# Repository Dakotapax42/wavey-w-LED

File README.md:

# wavey-w-LED

temporary repository until I finalize things :)

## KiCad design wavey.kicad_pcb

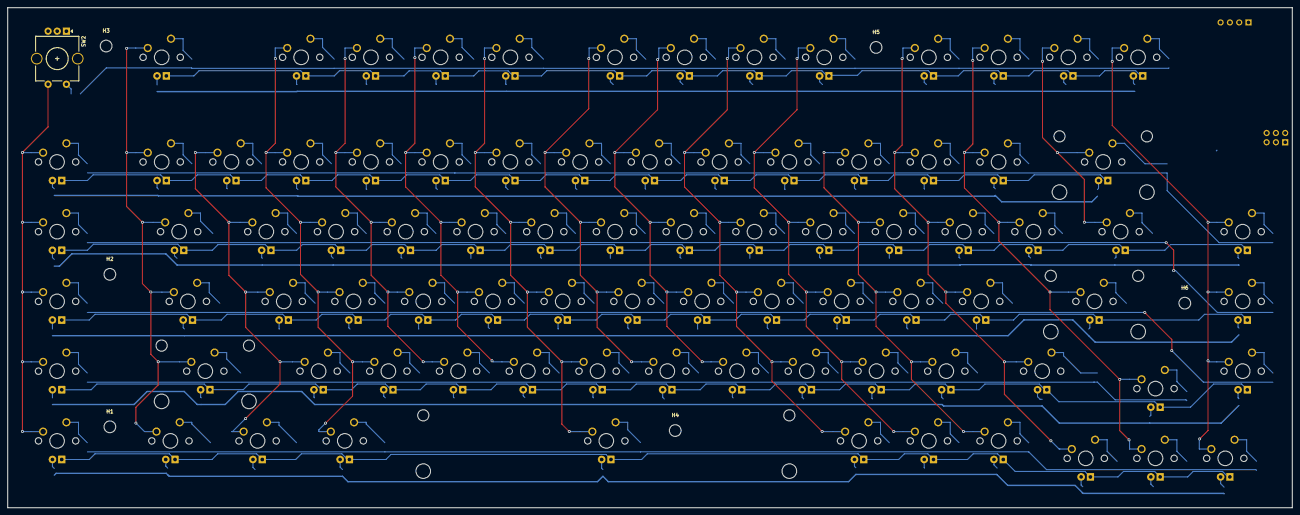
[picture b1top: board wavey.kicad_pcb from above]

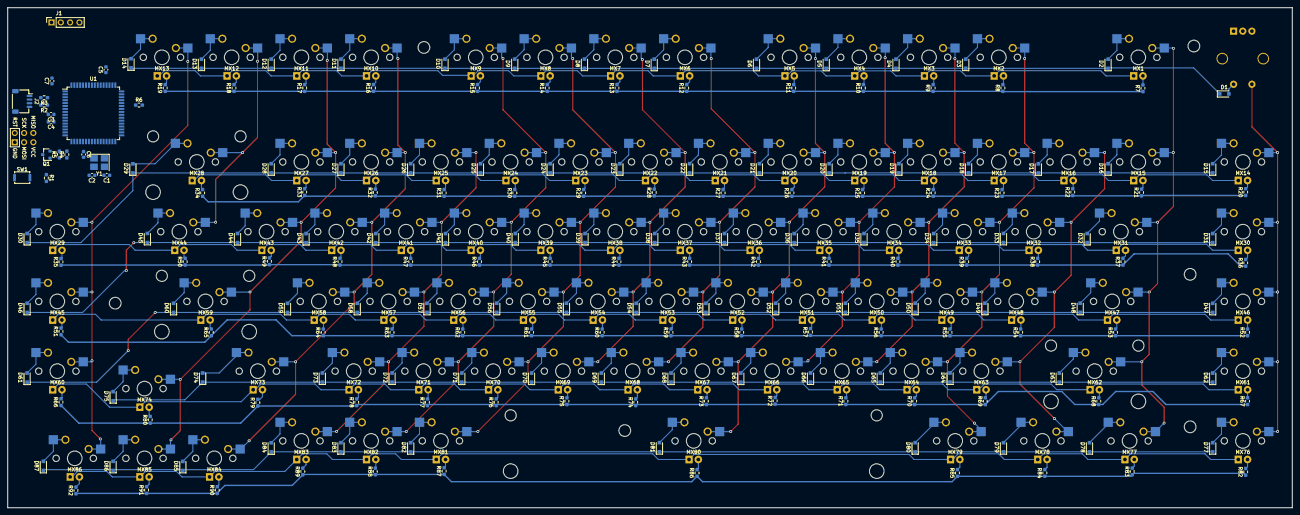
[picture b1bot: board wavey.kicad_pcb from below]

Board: 2 copper layers, 350.9 x 136.6 mm, 283 parts (191 on the bottom side), 214 nets.

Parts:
C1, C2: 22pF; C_0603_1608Metric
C3: 1uF; C_0603_1608Metric
C4, C5, C6: 0.1uF; C_0603_1608Metric
C7: 10uF; C_0603_1608Metric
D1, D2, D3, D4, D5, D6, D7, D8, D9, D10, D11, D12, D13, D14, D15, D16, D17, D18, D19, D20, D21, D22, D23, D24, D25, D26, D27, D28, D29, D30, D31, D32, D33, D34, D35, D36, D37, D38, D39, D40, D41, D42, D43, D44, D45, D46, D47, D48, D49, D50, D51, D52, D53, D54, D55, D56, D57, D58, D59, D60, D61, D62, D63, D64, D65, D66, D67, D68, D69, D70, D71, D72, D73, D74, D75, D77, D78, D79, D80, D81, D82, D83, D84, D85, D86, D87: D_Small; D_SOD-323_HandSoldering
H1, H2, H3, H4, H5, H6: MountingHole; MountingHole_3.2mm_M3
J1: Conn_01x04; PinSocket_1x04_P2.54mm_Vertical
J2: Conn_01x04; JST_SH_SM04B-SRSS-TB_1x04-1MP_P1.00mm_Horizontal
J3: AVR-ISP-6; Reset_Pretty-Mask
MX1, MX2, MX3, MX4, MX5, MX6, MX7, MX8, MX9, MX10, MX11, MX12, MX13, MX14, MX15, MX16, MX17, MX18, MX19, MX20, MX21, MX22, MX23, MX24, MX25, MX26, MX27, MX29, MX30, MX32, MX33, MX34, MX35, MX36, MX37, MX38, MX39, MX40, MX41, MX42, MX43, MX45, MX46, MX48, MX49, MX50, MX51, MX52, MX53, MX54, MX55, MX56, MX57, MX58, MX60, MX61, MX63, MX64, MX65, MX66, MX67, MX68, MX69, MX70, MX71, MX72, MX74, MX76, MX81, MX82, MX83, MX84, MX85, MX86: MX-LED; MXOnly-1U-Hotswap
MX28: MX-LED; MXOnly-2U-Hotswap
MX31, MX44: MX-LED; MXOnly-1.5U-Hotswap
MX47, MX73: MX-LED; MXOnly-1.75U-Hotswap
MX59, MX62: MX-LED; MXOnly-2.25U-Hotswap
MX77, MX78, MX79: MX-LED; MXOnly-1.25U-Hotswap
MX80: MX-LED; MXOnly-6.25U-Hotswap
Q1: AO3400A; SOT-23
R1, R5: 10k; R_0603_1608Metric_Pad0.98x0.95mm_HandSolder
R2, R3: 22; R_0603_1608Metric_Pad0.98x0.95mm_HandSolder
R4, R7, R8, R9, R10, R11, R12, R13, R14, R15, R16, R17, R18, R19, R20, R21, R22, R23, R24, R25, R26, R27, R28, R29, R30, R31, R32, R33, R34, R35, R36, R37, R38, R39, R40, R41, R42, R43, R44, R45, R46, R47, R48, R49, R50, R51, R52, R53, R54, R55, R56, R57, R58, R59, R60, R61, R62, R63, R64, R65, R66, R67, R68, R69, R70, R71, R72, R73, R74, R75, R76, R77, R78, R79, R80, R82, R83, R84, R85, R86, R87, R88, R89, R90, R91, R92: 470; R_0603_1608Metric_Pad0.98x0.95mm_HandSolder
R6: 1k; R_0603_1608Metric_Pad0.98x0.95mm_HandSolder
SW1: SW_Push; SW_Push_SPST_NO_Alps_SKRK
SW2: Rotary_Encoder_Switch; RotaryEncoder_Alps_EC11E-Switch_Vertical_H20mm_CircularMoun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
U1: AT90USB1286-AU; TQFP-64_14x14mm_P0.8mm
Y1: 16Mhz; Crystal_SMD_3225-4Pin_3.2x2.5mm_HandSoldering

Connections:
+5V: C4.1, C5.1, C6.1, C7.1, J1.3, J2.1, J3.2, R1.1, R7.1, R8.1, R9.1, R10.1, R11.1, R12.1, R13.1, R14.1, R15.1, R16.1, R17.1, R18.1, R19.1, R20.1, R21.1, R22.1, R23.1, R24.1, R25.1, R26.1, R27.1, R28.1, R29.1, R30.1, R31.1, R32.1, R33.1, R34.1, R35.1, R36.1, R37.1, R38.1, R39.1, R40.1, R41.1, R42.1, R43.1, R44.1, R45.1, R46.1, R47.1, R48.1, R49.1, R50.1, R51.1, R52.1, R53.1, R54.1, R55.1, R56.1, R57.1, R58.1, R59.1, R60.1, R61.1, R62.1, R63.1, R64.1, R65.1, R66.1, R67.1, R68.1, R69.1, R70.1, R71.1, R72.1, R73.1, R74.1, R75.1, R76.1, R77.1, R78.1, R79.1, R80.1, R82.1, R83.1, R84.1, R85.1, R86.1, R87.1, R88.1, R89.1, R90.1, R91.1, R92.1, U1.3, U1.8, U1.21, U1.52, U1.64
/MCU_D+: R2.1, U1.5
/MCU_D-: R3.1, U1.4
A1: SW2.A, U1.14
B1: SW2.B, U1.15
D+: J2.3, R2.2
D-: J2.2, R3.2
GND: C1.2, C2.1, C3.2, C4.2, C5.2, C6.2, C7.2, J1.4, J2.4, J3.6, Q1.2, R5.2, R6.2, SW1.1, SW2.C, U1.6, U1.22, U1.53, U1.63, Y1.2, Y1.4
LEGEND: MX1.4, MX2.4, MX3.4, MX4.4, MX5.4, MX6.4, MX7.4, MX8.4, MX9.4, MX10.4, MX11.4, MX12.4, MX13.4, MX14.4, MX15.4, MX16.4, MX17.4, MX18.4, MX19.4, MX20.4, MX21.4, MX22.4, MX23.4, MX24.4, MX25.4, MX26.4, MX27.4, MX28.4, MX29.4, MX30.4, MX31.4, MX32.4, MX33.4, MX34.4, MX35.4, MX36.4, MX37.4, MX38.4, MX39.4, MX40.4, MX41.4, MX42.4, MX43.4, MX44.4, MX45.4, MX46.4, MX47.4, MX48.4, MX49.4, MX50.4, MX51.4, MX52.4, MX53.4, MX54.4, MX55.4, MX56.4, MX57.4, MX58.4, MX59.4, MX60.4, MX61.4, MX62.4, MX63.4, MX64.4, MX65.4, MX66.4, MX67.4, MX68.4, MX69.4, MX70.4, MX71.4, MX72.4, MX73.4, MX74.4, MX76.4, MX77.4, MX78.4, MX79.4, MX80.4, MX81.4, MX82.4, MX83.4, MX84.4, MX85.4, MX86.4, Q1.3
unnamed: C1.1, U1.24, Y1.1
unnamed: C2.2, U1.23, Y1.3
unnamed: C3.1, U1.7
unnamed: D1.2, SW2.S2
unnamed: D2.2, MX1.2
unnamed: D3.2, MX2.2
unnamed: D4.2, MX3.2
unnamed: D5.2, MX4.2
unnamed: D6.2, MX5.2
unnamed: D7.2, MX6.2
unnamed: D8.2, MX7.2
unnamed: D9.2, MX8.2
unnamed: D10.2, MX9.2
unnamed: D11.2, MX10.2
unnamed: D12.2, MX11.2
unnamed: D13.2, MX12.2
unnamed: D14.2, MX13.2
unnamed: D15.2, MX14.2
unnamed: D16.2, MX15.2
unnamed: D17.2, MX16.2
unnamed: D18.2, MX17.2
unnamed: D19.2, MX18.2
unnamed: D20.2, MX19.2
unnamed: D21.2, MX20.2
unnamed: D22.2, MX21.2
unnamed: D23.2, MX22.2
unnamed: D24.2, MX23.2
unnamed: D25.2, MX24.2
unnamed: D26.2, MX25.2
unnamed: D27.2, MX26.2
unnamed: D28.2, MX27.2
unnamed: D29.2, MX28.2
unnamed: D30.2, MX29.2
unnamed: D31.2, MX30.2
unnamed: D32.2, MX31.2
unnamed: D33.2, MX32.2
unnamed: D34.2, MX33.2
unnamed: D35.2, MX34.2
unnamed: D36.2, MX35.2
unnamed: D37.2, MX36.2
unnamed: D38.2, MX37.2
unnamed: D39.2, MX38.2
unnamed: D40.2, MX39.2
unnamed: D41.2, MX40.2
unnamed: D42.2, MX41.2
unnamed: D43.2, MX42.2
unnamed: D44.2, MX43.2
unnamed: D45.2, MX44.2
unnamed: D46.2, MX45.2
unnamed: D47.2, MX46.2
unnamed: D48.2, MX47.2
unnamed: D49.2, MX48.2
unnamed: D50.2, MX49.2
unnamed: D51.2, MX50.2
unnamed: D52.2, MX51.2
unnamed: D53.2, MX52.2
unnamed: D54.2, MX53.2
unnamed: D55.2, MX54.2
unnamed: D56.2, MX55.2
unnamed: D57.2, MX56.2
unnamed: D58.2, MX57.2
unnamed: D59.2, MX58.2
unnamed: D60.2, MX59.2
unnamed: D61.2, MX60.2
unnamed: D62.2, MX61.2
unnamed: D63.2, MX62.2
unnamed: D64.2, MX63.2
unnamed: D65.2, MX64.2
unnamed: D66.2, MX65.2
unnamed: D67.2, MX66.2
unnamed: D68.2, MX67.2
unnamed: D69.2, MX68.2
unnamed: D70.2, MX69.2
unnamed: D71.2, MX70.2
unnamed: D72.2, MX71.2
unnamed: D73.2, MX72.2
unnamed: D74.2, MX73.2
unnamed: D75.2, MX74.2
unnamed: D77.2, MX76.2
unnamed: D78.2, MX77.2
unnamed: D79.2, MX78.2
unnamed: D80.2, MX79.2
unnamed: D81.2, MX80.2
unnamed: D82.2, MX81.2
unnamed: D83.2, MX82.2
unnamed: D84.2, MX83.2
unnamed: D85.2, MX84.2
unnamed: D86.2, MX85.2
unnamed: D87.2, MX86.2
unnamed: J3.1, U1.13
unnamed: J3.3, U1.11
unnamed: J3.4, U1.12
unnamed: MX1.3, R7.2
unnamed: MX2.3, R8.2
unnamed: MX3.3, R9.2
unnamed: MX4.3, R10.2
unnamed: MX5.3, R11.2
unnamed: MX6.3, R12.2
unnamed: MX7.3, R13.2
unnamed: MX8.3, R14.2
unnamed: MX9.3, R15.2
unnamed: MX10.3, R16.2
unnamed: MX11.3, R17.2
unnamed: MX12.3, R18.2
unnamed: MX13.3, R19.2
unnamed: MX14.3, R20.2
unnamed: MX15.3, R21.2
unnamed: MX16.3, R22.2
unnamed: MX17.3, R23.2
unnamed: MX18.3, R24.2
unnamed: MX19.3, R25.2
unnamed: MX20.3, R26.2
unnamed: MX21.3, R27.2
unnamed: MX22.3, R28.2
unnamed: MX23.3, R29.2
unnamed: MX24.3, R30.2
unnamed: MX25.3, R31.2
unnamed: MX26.3, R32.2
unnamed: MX27.3, R33.2
unnamed: MX28.3, R34.2
unnamed: MX29.3, R35.2
unnamed: MX30.3, R36.2
unnamed: MX31.3, R37.2
unnamed: MX32.3, R38.2
unnamed: MX33.3, R39.2
unnamed: MX34.3, R40.2
unnamed: MX35.3, R41.2
unnamed: MX36.3, R42.2
unnamed: MX37.3, R43.2
unnamed: MX38.3, R44.2
unnamed: MX39.3, R45.2
unnamed: MX40.3, R46.2
unnamed: MX41.3, R47.2
unnamed: MX42.3, R48.2
unnamed: MX43.3, R49.2
unnamed: MX44.3, R50.2
unnamed: MX45.3, R51.2
unnamed: MX46.3, R52.2
unnamed: MX47.3, R53.2
unnamed: MX48.3, R54.2
unnamed: MX49.3, R55.2
unnamed: MX50.3, R56.2
unnamed: MX51.3, R57.2
unnamed: MX52.3, R58.2
unnamed: MX53.3, R59.2
unnamed: MX54.3, R60.2
unnamed: MX55.3, R61.2
unnamed: MX56.3, R62.2
unnamed: MX57.3, R63.2
unnamed: MX58.3, R64.2
unnamed: MX59.3, R65.2
unnamed: MX60.3, R66.2
unnamed: MX61.3, R67.2
unnamed: MX62.3, R68.2
unnamed: MX63.3, R69.2
unnamed: MX64.3, R70.2
unnamed: MX65.3, R71.2
unnamed: MX66.3, R72.2
unnamed: MX67.3, R73.2
unnamed: MX68.3, R74.2
unnamed: MX69.3, R75.2
unnamed: MX70.3, R76.2
unnamed: MX71.3, R77.2
unnamed: MX72.3, R78.2
unnamed: MX73.3, R79.2
unnamed: MX74.3, R80.2
unnamed: MX76.3, R82.2
unnamed: MX77.3, R83.2
unnamed: MX78.3, R84.2
unnamed: MX79.3, R85.2
unnamed: MX80.3, R86.2
unnamed: MX81.3, R87.2
unnamed: MX82.3, R88.2
unnamed: MX83.3, R89.2
unnamed: MX84.3, R90.2
unnamed: MX85.3, R91.2
unnamed: MX86.3, R92.2
unnamed: Q1.1, R4.1, R5.1
unnamed: R4.2, U1.17
unnamed: R6.1, U1.43
RESET: J3.5, R1.2, SW1.2, U1.20
SCL: J1.2, U1.25
SDA: J1.1, U1.26
col0: MX14.1, MX30.1, MX46.1, MX61.1, MX76.1, SW2.S1
col1: MX1.1, MX15.1, MX31.1, MX47.1, MX62.1, MX77.1
col2: MX16.1, MX32.1, MX48.1, MX63.1, MX78.1
col3: MX2.1, MX17.1, MX33.1, MX49.1, MX64.1, MX79.1
col4: MX3.1, MX18.1, MX34.1, MX50.1, MX65.1
col5: MX4.1, MX19.1, MX35.1, MX51.1, MX66.1
col6: MX5.1, MX20.1, MX36.1, MX52.1, MX67.1, MX80.1
col7: MX6.1, MX21.1, MX37.1, MX53.1, MX68.1
col8: MX7.1, MX22.1, MX38.1, MX54.1, MX69.1
col9: MX8.1, MX23.1, MX39.1, MX55.1, MX70.1, MX81.1
col10: MX9.1, MX24.1, MX40.1, MX56.1, MX71.1, MX82.1
col11: MX25.1, MX41.1, MX57.1, MX72.1, MX83.1
col12: MX10.1, MX26.1, MX42.1, MX58.1, MX73.1, MX84.1
col13: MX11.1, MX27.1, MX43.1, MX59.1, MX74.1, MX85.1
col14: MX12.1, MX28.1, MX44.1
col15: MX13.1, MX29.1, MX45.1, MX60.1, MX86.1
row0: D1.1, D2.1, D3.1, D4.1, D5.1, D6.1, D7.1, D8.1, D9.1, D10.1, D11.1, D12.1, D13.1, D14.1
row1: D15.1, D16.1, D17.1, D18.1, D19.1, D20.1, D21.1, D22.1, D23.1, D24.1, D25.1, D26.1, D27.1, D28.1, D29.1, D30.1
row2: D31.1, D32.1, D33.1, D34.1, D35.1, D36.1, D37.1, D38.1, D39.1, D40.1, D41.1, D42.1, D43.1, D44.1, D45.1, D46.1
row3: D47.1, D48.1, D49.1, D50.1, D51.1, D52.1, D53.1, D54.1, D55.1, D56.1, D57.1, D58.1, D59.1, D60.1, D61.1
row4: D62.1, D63.1, D64.1, D65.1, D66.1, D67.1, D68.1, D69.1, D70.1, D71.1, D72.1, D73.1, D74.1, D75.1
row5: D77.1, D78.1, D79.1, D80.1, D81.1, D82.1, D83.1, D84.1, D85.1, D86.1, D87.1
